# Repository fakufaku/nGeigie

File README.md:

A repositroy to host firmware/software related to the DIY Geiger-Mueller
counter units.

**This version of the code is set to run on old school Freakduino+NetRAD+LND712 hardware.**

http://www.tokyohackerspace.org/en/event/diy-geiger-mueller-counter-workshop-20-2011-08-08
http://www.tokyohackerspace.org/en/event/diy-geiger-mueller-counter-workshop-20-2011-08-22

See this for more insights on the history of this kit:
http://tokyohackerspace.org/en/blog/tokyo-hackerspacerdtn-geiger-shield-dev-history

This kit is a THS[1] project in collaboration with SafeCast[2]. Once you buy
and build your device, you own it (hardware and software) and the data it
produces. You can opt-in to have your data logged to the THS account on
Pachube[3] (for free) and have it available to the public (for free).

[1]	http://tokyohackerspace.org/
[2]	http://safecast.org/
[3]	http://pachube.com/feeds?user=tokyohackerspace

To be able to update/change the firmware of your DIY GM counter, you'll need:
a) a toolchain to build (compile/link) the source for the Arduino
b) a tool to upload the binary to the flash of the Arduino
c) way to access the source code and related libraries

One relatively simple way is to download the appropriate "Arduino IDE" for your
OS of choice from http://arduino.cc/en/Main/Software since this provides both
a) and b) above.

If you are not into development just get a stable snapshot from
https://github.com/thinrope/NetRad-THS, otherwise use your favorte git tool to
improve the source and send pull requests.

To have your unit upload data to http://pachube.com/ you need to setup an
account with them, or use the THS shared account. To use the THS shared
account, please contact kalin@safecast.org and you'll be given an ID.

THIS IS A WORK IN PROGRESS, PLEASE BEAR WITH ME!
Feel free to submit issues on github, or contact the developers directly.

To use the bleeding edge, on Linux:

cd sketchbook
git clone https://github.com/thinrope/NetRad-THS.git
cd NetRad-THS/
git checkout testing
git submodule init
git submodule update
cd src/netrad_ths
make
make upload
make monitor

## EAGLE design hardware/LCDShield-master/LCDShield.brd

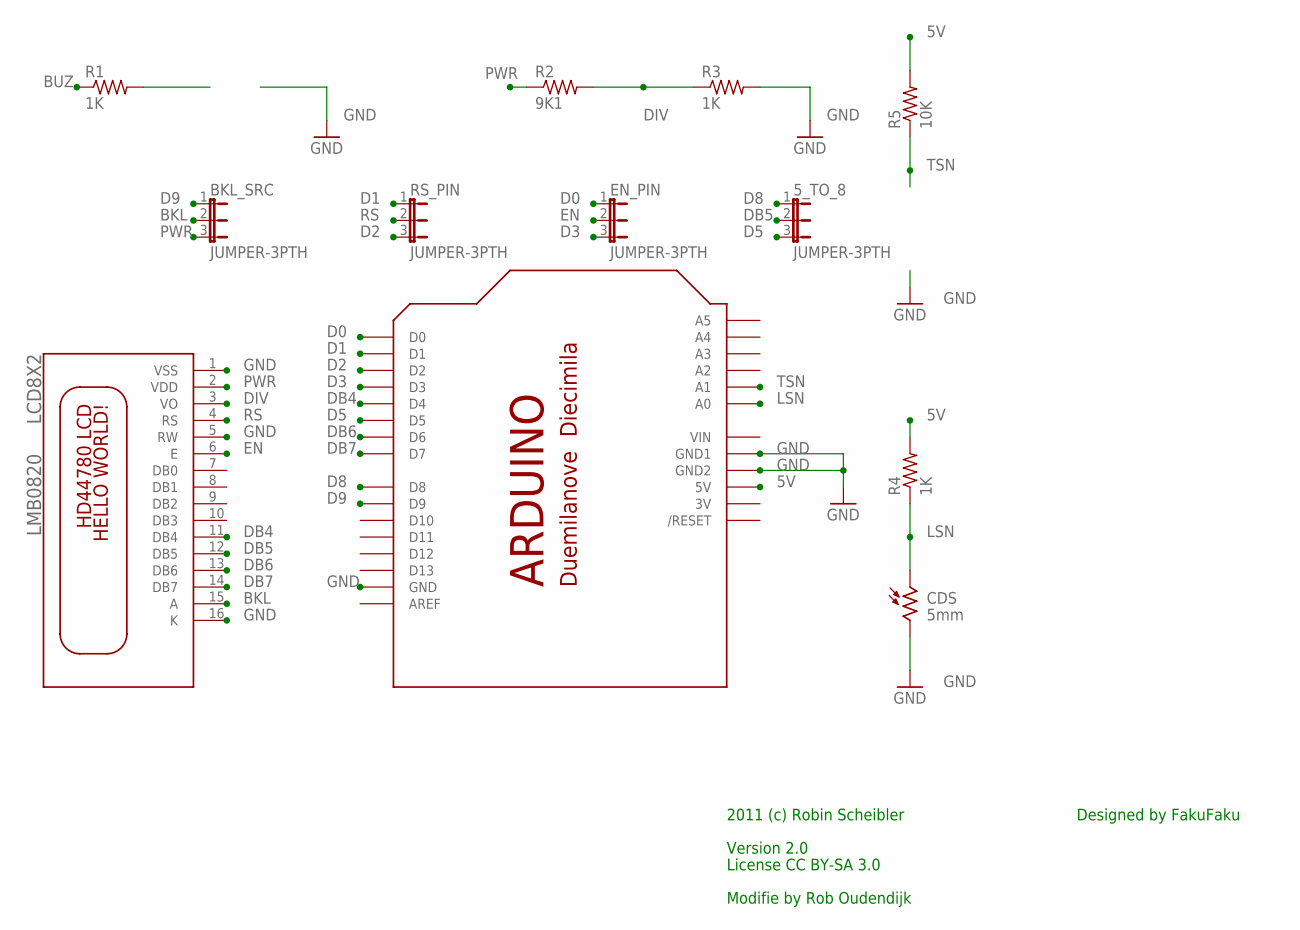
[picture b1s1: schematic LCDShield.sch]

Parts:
5_TO_8: JUMPER-3PTH; 1X03
BKL_SRC: JUMPER-3PTH; 1X03
CDS: 5mm; TO46-VT200
EN_PIN: JUMPER-3PTH; 1X03
LCD8X2: LMB0820
R1, R3, R4: 1K; 0207/10
R2: 9K1; 0207/10
R5: 10K; 0207/10
RS_PIN: JUMPER-3PTH; 1X03
SHIELD: ARDUINOSHIELD-NOHOLE; ARDUINO-NOHOLE

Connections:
3V: SHIELD.3V
5V: R4.2, R5.2, SHIELD.5V
BKL: BKL_SRC.2, LCD8X2.15 (A)
BUZ: R1.1
D0: EN_PIN.1, SHIELD.D0
D1: RS_PIN.1, SHIELD.D1
D2: RS_PIN.3, SHIELD.D2
D3: EN_PIN.3, SHIELD.D3
D5: 5_TO_8.3, SHIELD.D5
D8: 5_TO_8.1, SHIELD.D8
D9: BKL_SRC.1, SHIELD.D9
DB4: LCD8X2.11 (DB4), SHIELD.D4
DB5: 5_TO_8.2, LCD8X2.12 (DB5)
DB6: LCD8X2.13 (DB6), SHIELD.D6
DB7: LCD8X2.14 (DB7), SHIELD.D7
DIV: LCD8X2.3 (VO), R2.2, R3.1
EN: EN_PIN.2, LCD8X2.6 (E)
GND: CDS.2, LCD8X2.1 (VSS), LCD8X2.5 (RW), LCD8X2.16 (K), R3.2, SHIELD.GND, SHIELD.GND1, SHIELD.GND2
LSN: CDS.1, R4.1, SHIELD.A0
PWR: BKL_SRC.3, LCD8X2.2 (VDD), R2.1
RS: LCD8X2.4 (RS), RS_PIN.2
TSN: R5.1, SHIELD.A1
VIN: SHIELD.VIN

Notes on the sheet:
Version 2.0
License CC BY-SA 3.0
Designed by FakuFaku
2011 (c) Robin Scheibler
Modifie by Rob Oudendijk

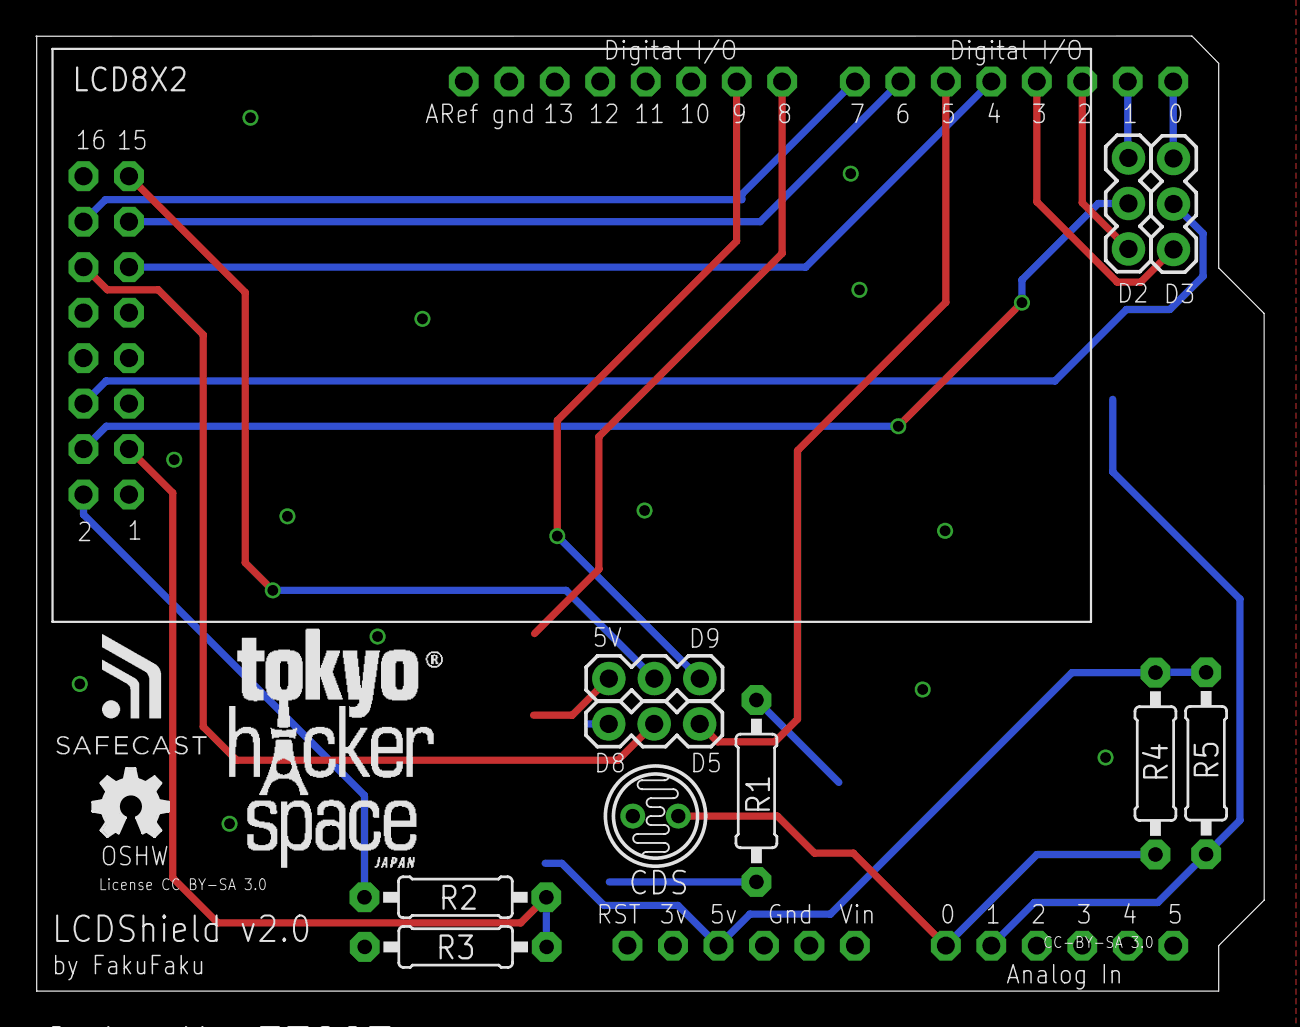
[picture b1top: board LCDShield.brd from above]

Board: 2 copper layers, 68.6 x 53.3 mm, 14 parts (0 on the bottom side), 20 nets.

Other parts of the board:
U$1: THS
U$4: OSHW_FILLX150_NOTEXT

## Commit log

2013-11-11 V1.1.3
2013-11-11 V 1.1.3
    5 minutes update setup
2013-11-20 V1.2.0
    Added display support. Code mostly done by Allan Lind
2013-11-20 Updated readme for display use
2013-11-21 Update nGeigie.ino
    Added LED Flash
2013-11-22 Updated borad settings
2013-11-22 Moved folders
2013-11-22 cleanup
2013-11-22 Setup for 5 minutes reporting to server
2013-11-23 removed old files
2013-12-20 V1.2.0 LCD version based on Ninja LCD shield
2013-12-20 Updated Readme file for V1.2.0
2014-02-04 V2.1
    LCD and SD card setup
2014-02-05 V2.1.2
    Fixe dual sensor test mistake
2014-02-07 V2.1.3
    SDfat library added and SDcard config
2014-02-07 Added A3GS library
    also included tests for testing A3GS shield
2014-04-08 V2.1.4
    Changed gateway to ngeigie.safecast.org 107.161.164.166
2014-04-08 V2.1.4 hex file added
2014-04-11 V2.1.5
    Switched gateways
2014-04-11 Update board_specific_settings.h
    V2.1.5 gateway switch
2014-07-26 Updated new nGeigie code to run on old school Freakduino+NetRAD+LND712 hardware.
2014-07-26 Note in README about this code version.
2014-07-26 Corrected server post command for ngeigie.safecast.org
